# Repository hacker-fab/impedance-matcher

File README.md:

# Automated Impedance Matcher

Teensy 4.1 control loop firmware, custom PCB/CAD hardware, and Python telemetry logging/plotting tools.

## Layout

```
├── firmware/
│   ├── impedance_matcher/                 # Tuning loop, local UI, & motor controls
│   ├── headless_matcher/                  # Serial-only sketch
│   ├── live.py                            # Serial reader, live plots, CSV logger
│   └── plot.py                            # Offline plots & Mermaid export
└── hardware/
    ├── CAD/                               # Mechanical design & enclosure models
    └── PCB/                               # KiCad project & manufacturing files
        ├── impedance_matcher.kicad_pro    # KiCad project main file
        ├── spice/                         # SPICE verification of analog support circuits
        └── production/                    # JLCPCB manufacturing & assembly
            ├── imp_match.zip              # Gerbers
            ├── imp_match_bom.csv          # Assembly BOM
            └── imp_match_positions.csv    # Component placement
```

**Arduino libraries:** Adafruit SSD1306, Adafruit GFX, and TMCStepper (GUI build); TMCStepper only for headless.

## Firmware

- **GUI:** Gradient-style matching toward lower VSWR; loop runs matching, encoder poll, then OLED refresh.
- **Headless:** Same matching; control via serial (`stream on`, `help`, etc.).

Serial is **500000** baud unless you change it in code and in `live.py`.

## Live telemetry

- Default CSV path is `data/csv/latest.csv`.
- Enable **`VSWR_CSV`** lines from the device: **USB log** in settings, or `stream on` in headless.

```bash
# From repo root; adjust --port to your Teensy
python firmware/live.py --port /dev/cu.usbmodemXXXX --window-seconds 20
```

## Offline plots

- Loads the 8-column telemetry CSV, drops bad/outlier rows, then plots VSWR, motors, and match state.
- **Matplotlib** is the default windowed plot.
- **Plotly:** `--interactive` (browser) or `--html`.
- **Mermaid:** `--mermaid` writes `data/mermaid/<csv_stem>_{vswr,motor1,motor2,match}.mmd`.
```bash
python firmware/plot.py path/to/run.csv
python firmware/plot.py path/to/run.csv --minutes --sample-interval 0.25
python firmware/plot.py path/to/run.csv --interactive
python firmware/plot.py path/to/run.csv --html
python firmware/plot.py path/to/run.csv --mermaid
```

## Telemetry CSV format

Written by `live.py` (and compatible with `plot.py`):

`host_time_s,device_millis,vswr,forward_v,reverse_v,motor1_pos_rad,motor2_pos_rad,at_match`

## Hardware notes

The analog support circuits have limited DC SPICE benches and worst-case
calculations; see `hardware/PCB/spice/` for their assumptions and limits.

`MATCHING_USE_DRIVER_UART` defaults to `0` in
`firmware/impedance_matcher/include/config.h` for standalone STEP/DIR. Set it to
`1` to enable TMC2209 UART. To return to standalone, reflash with `0` and fully
power-cycle both drivers (VM and VIO); a Teensy-only reset does not clear their
registers.

Before using external 5 V and USB together, isolate the Teensy's VIN–VUSB link
following [PJRC's power instructions](https://www.pjrc.com/store/teensy41.html).

## Authors

- Miguel Salvacion
- William Gao

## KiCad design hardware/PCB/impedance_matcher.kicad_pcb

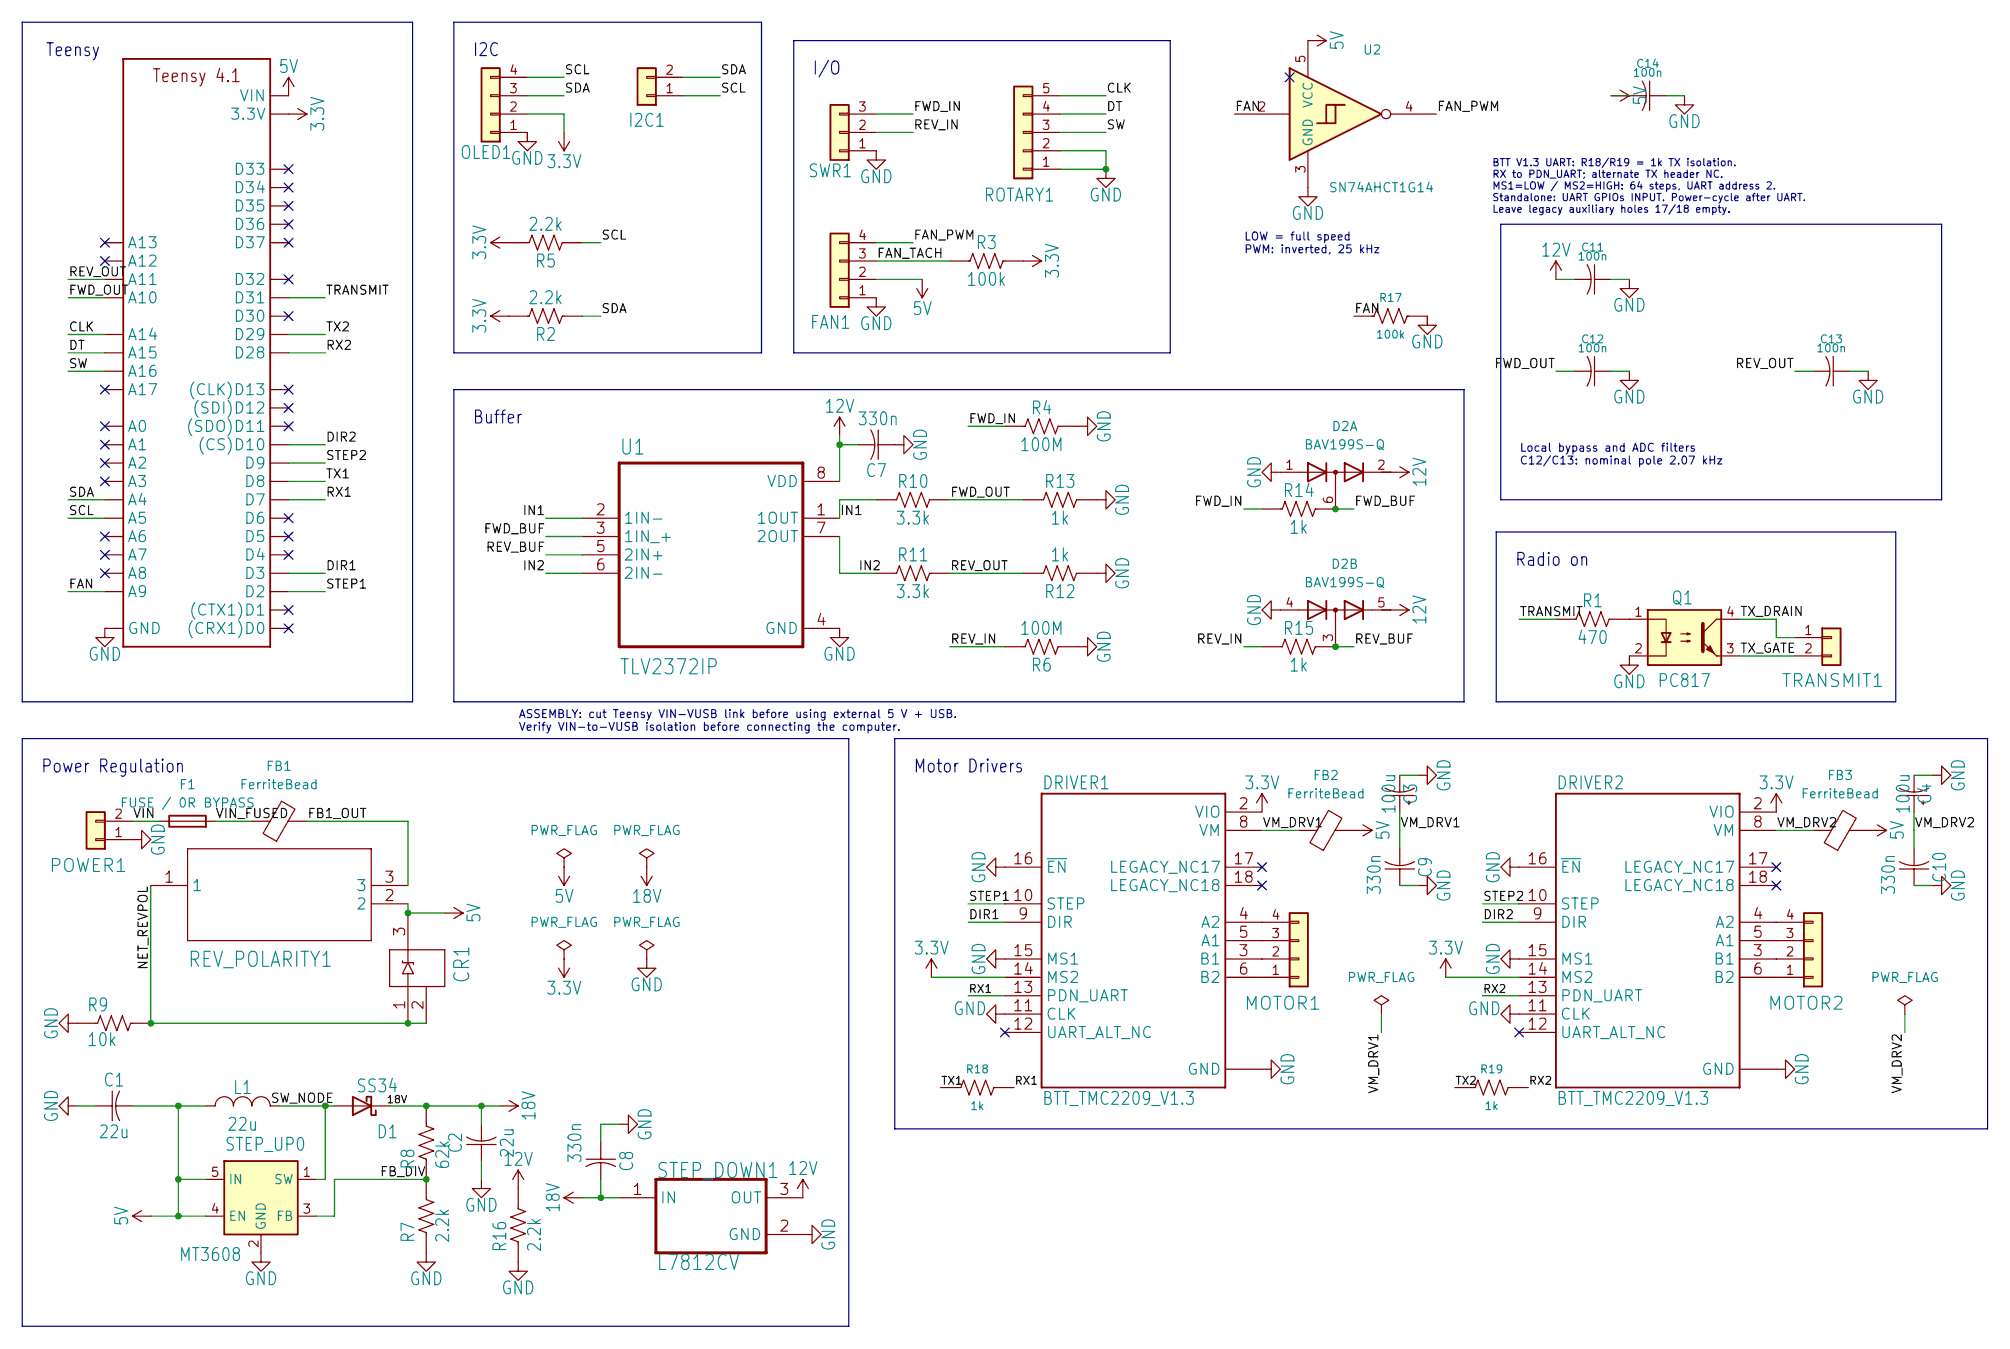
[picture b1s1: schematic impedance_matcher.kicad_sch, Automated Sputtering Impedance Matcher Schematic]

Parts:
A1: TEENSY_4.1; TEENSY_LONG_EXT; MPN TEENSY41
C1, C2: 22u; CAPC2012X110; MPN CL21A226MAQNNNE; LCSC Part C45783
C3, C4: 100u; CP_Radial_D5.0mm_P5.08mm_Formed; MPN EEU-FR1C101B
C7, C8, C9, C10: 330n; CAPC2012X110; MPN 0805B334K500NT; LCSC Part C1740
C11, C12, C13, C14: 100n; CAPC2012X110; MPN CC0805KRX7R9BB104; LCSC Part C49678
CR1: BZX84C5V6; SOT95P240X110-3N; MPN BZX84C5V6; LCSC Part C148101
D1: SS34; SMB_ONS; MPN SS34; LCSC Part C8678
D2: BAV199S-Q; SOT-363_SC-70-6; MPN BAV199S-QZ; LCSC Part C7507590
DRIVER1, DRIVER2: BTT_TMC2209_V1.3; MODULE_TMC2209_SILENTSTEPSTICK; MPN TMC2209 V1.3
F1: FUSE / 0R BYPASS; Fuse_1206_3216Metric
FAN1: Conn_01x04; JST_PH_B4B-PH-K_1x04_P2.00mm_Vertical; MPN B4B-PH-K-S
FB1, FB2, FB3: FerriteBead; L_0805_2012Metric; MPN MPZ2012S101AT000; LCSC Part C15957
I2C1: Conn_01x02; JST_PH_B2B-PH-K_1x02_P2.00mm_Vertical; MPN B2B-PH-K-S
L1: 22u; INDM5450X580; MPN SMNR5040-220MT; LCSC Part C9391
MOTOR1, MOTOR2: Conn_01x04; JST-4-PTH-VERT; MPN B4B-PH-K-S
OLED1: Conn_01x04; JST_PH_B4B-PH-K_1x04_P2.00mm_Vertical; MPN B4B-PH-K-S
POWER1: Conn_01x02; 1X02_2.54_SCREWTERM; MPN PRT-10571
Q1: PC817; DIP762W50P254L650H455Q4B; MPN PC817B; LCSC Part C20612593
R1: 470; RESC2012X65; MPN 0805W8F4700T5E; LCSC Part C17710
R2, R5, R7: 2.2k; RESC2012X65; MPN 0805W8F2201T5E; LCSC Part C17520
R3, R17: 100k; RESC2012X65; MPN 0805W8F1003T5E; LCSC Part C149504
R4, R6: 100M; RESC2012X65; MPN RC0805JR-07100ML; LCSC Part C137480
R8: 62k; RESC2012X65; MPN 0805W8F6202T5E; LCSC Part C17783
R9: 10k; RESC2012X65; MPN 0805W8F1002T5E; LCSC Part C17414
R10, R11: 3.3k; RESC2012X65; MPN 0805W8F3301T5E; LCSC Part C26010
R12, R13, R14, R15, R18, R19: 1k; RESC2012X65; MPN 0805W8F1001T5E; LCSC Part C17513
R16: 2.2k; R_0805_2012Metric; MPN 0805W8F2201T5E; LCSC Part C17520
REV_POLARITY1: DMP6180SK3-13TO252_DMP6180SK3_DIO; TO252_DMP6180SK3_DIO; MPN DMP6180SK3-13; LCSC Part C93034
ROTARY1: Conn_01x05; JST_PH_B5B-PH-K_1x05_P2.00mm_Vertical; MPN B5B-PH-K-S
STEP_DOWN1: L7812CV; TO-220-3; MPN L7812CV; LCSC Part C105651
STEP_UP0: MT3608; SOT95P280X145-6N; MPN MT3608; LCSC Part C84817
SWR1: JST_03; JST_PH_B3B-PH-K_1x03_P2.00mm_Vertical; MPN B3B-PH-K-S
TRANSMIT1: Conn_01x02; 1X02_2.54_SCREWTERM; MPN PRT-10571
U1: TLV2372IP; DIP794W45P254L959H508Q8; MPN TLV2372IP; LCSC Part C2878991
U2: SN74AHCT1G14; SOT-23-5; MPN SN74AHCT1G14DBVR; LCSC Part C55250

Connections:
3.3V: A1.3V3 (3.3V), A1.3V3@2 (3.3V), DRIVER1.2 (VIO_2), DRIVER1.14 (MS2_14), DRIVER2.2 (VIO_2), DRIVER2.14 (MS2_14), OLED1.2, R2.2, R3.2, R5.2
5V: A1.VIN, C1.2, C14.2, CR1.3, FAN1.2, FB2.2, FB3.2, L1.1, REV_POLARITY1.2, STEP_UP0.4 (EN), STEP_UP0.5 (IN), U2.5 (VCC)
12V: C7.2, C11.2, D2.2 (K2), D2.5 (K4), R16.2, STEP_DOWN1.3 (OUT), U1.8 (VDD)
18V: C2.2, C8.2, D1.1 (K), R8.2, STEP_DOWN1.1 (IN)
/CLK: A1.D38 (A14), ROTARY1.5
/DIR1: A1.D3, DRIVER1.9 (DIR_9)
/DIR2: A1.D10 ((CS)D10), DRIVER2.9 (DIR_9)
/DT: A1.D39 (A15), ROTARY1.4
/FAN: A1.D23 (A9), R17.1, U2.2
/FAN_PWM: FAN1.4, U2.4
/FAN_TACH: FAN1.3, R3.1
/FB1_OUT: FB1.2, REV_POLARITY1.3
/FB_DIV: R7.2, R8.1, STEP_UP0.3 (FB)
/FWD_BUF: D2.6 (K3A4), R14.2, U1.3 (1IN_+)
/FWD_IN: R4.1, R14.1, SWR1.3
/FWD_OUT: A1.D24 (A10), C12.2, R10.2, R13.1
/IN1: R10.1, U1.1 (1OUT), U1.2 (1IN-)
/IN2: R11.1, U1.6 (2IN-), U1.7 (2OUT)
/NET_REVPOL: CR1.1, CR1.2, R9.2, REV_POLARITY1.1
/REV_BUF: D2.3 (K1A2), R15.2, U1.5 (2IN+)
/REV_IN: R6.2, R15.1, SWR1.2
/REV_OUT: A1.D25 (A11), C13.2, R11.2, R12.2
/RX1: A1.D7, DRIVER1.13 (PDN_UART), R18.2
/RX2: A1.D28, DRIVER2.13 (PDN_UART), R19.2
/SCL: A1.D19 (A5), I2C1.1, OLED1.4, R5.1
/SDA: A1.D18 (A4), I2C1.2, OLED1.3, R2.1
/STEP1: A1.D2, DRIVER1.10 (STEP_10)
/STEP2: A1.D9, DRIVER2.10 (STEP_10)
/SW: A1.D40 (A16), ROTARY1.3
/SW_NODE: D1.2 (A), L1.2, STEP_UP0.1 (SW)
/TRANSMIT: A1.D31, R1.1
/TX1: A1.D8, R18.1
/TX2: A1.D29, R19.1
/TX_DRAIN: Q1.4, TRANSMIT1.1
/TX_GATE: Q1.3, TRANSMIT1.2
/VIN: F1.1, POWER1.2
/VIN_FUSED: F1.2, FB1.1
/VM_DRV1: C3.1 (+), C9.2, DRIVER1.8 (VM_8), FB2.1
/VM_DRV2: C4.1 (+), C10.2, DRIVER2.8 (VM_8), FB3.1
GND: A1.AGND/GND (GND), A1.GND, A1.GND@2 (GND), C1.1, C2.1, C3.2 (-), C4.2 (-), C7.1, C8.1, C9.1, C10.1, C11.1, C12.1, C13.1, C14.1, D2.1 (A1), D2.4 (A3), DRIVER1.1 (GND_1), DRIVER1.7 (GND_7), DRIVER1.11 (CLK), DRIVER1.15 (MS1_15), DRIVER1.16 (~EN_16), DRIVER2.1 (GND_1), DRIVER2.7 (GND_7), DRIVER2.11 (CLK), DRIVER2.15 (MS1_15), DRIVER2.16 (~EN_16), FAN1.1, OLED1.1, POWER1.1, Q1.2, R4.2, R6.1, R7.1, R9.1, R12.1, R13.2, R16.1, R17.2, ROTARY1.1, ROTARY1.2, STEP_DOWN1.2 (GND), STEP_UP0.2 (GND), SWR1.1, U1.4 (GND), U2.3 (GND)
unnamed: DRIVER1.5 (A1), MOTOR1.3
unnamed: DRIVER1.4 (B1), MOTOR1.4
unnamed: DRIVER1.3 (B2), MOTOR1.2
unnamed: DRIVER1.6 (A2), MOTOR1.1
unnamed: DRIVER2.5 (A1), MOTOR2.3
unnamed: DRIVER2.4 (B1), MOTOR2.4
unnamed: DRIVER2.3 (B2), MOTOR2.2
unnamed: DRIVER2.6 (A2), MOTOR2.1
unnamed: Q1.1, R1.2

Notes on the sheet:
LOW = full speed PWM: inverted, 25 kHz
I2C
Motor Drivers
Power Regulation
Radio on
I/O
Local bypass and ADC filters C12/C13: nominal pole 2.07 kHz
Teensy
ASSEMBLY: cut Teensy VIN-VUSB link before using external 5 V + USB. Verify VIN-to-VUSB isolation before connecting the computer.
Buffer
BTT V1.3 UART: R18/R19 = 1k TX isolation. RX to PDN_UART; alternate TX header NC. MS1=LOW / MS2=HIGH: 64 steps, UART address 2. Standalone: UART GPIOs INPUT. Power-cycle after UART. Leave legacy auxiliary holes 17/18 empty.

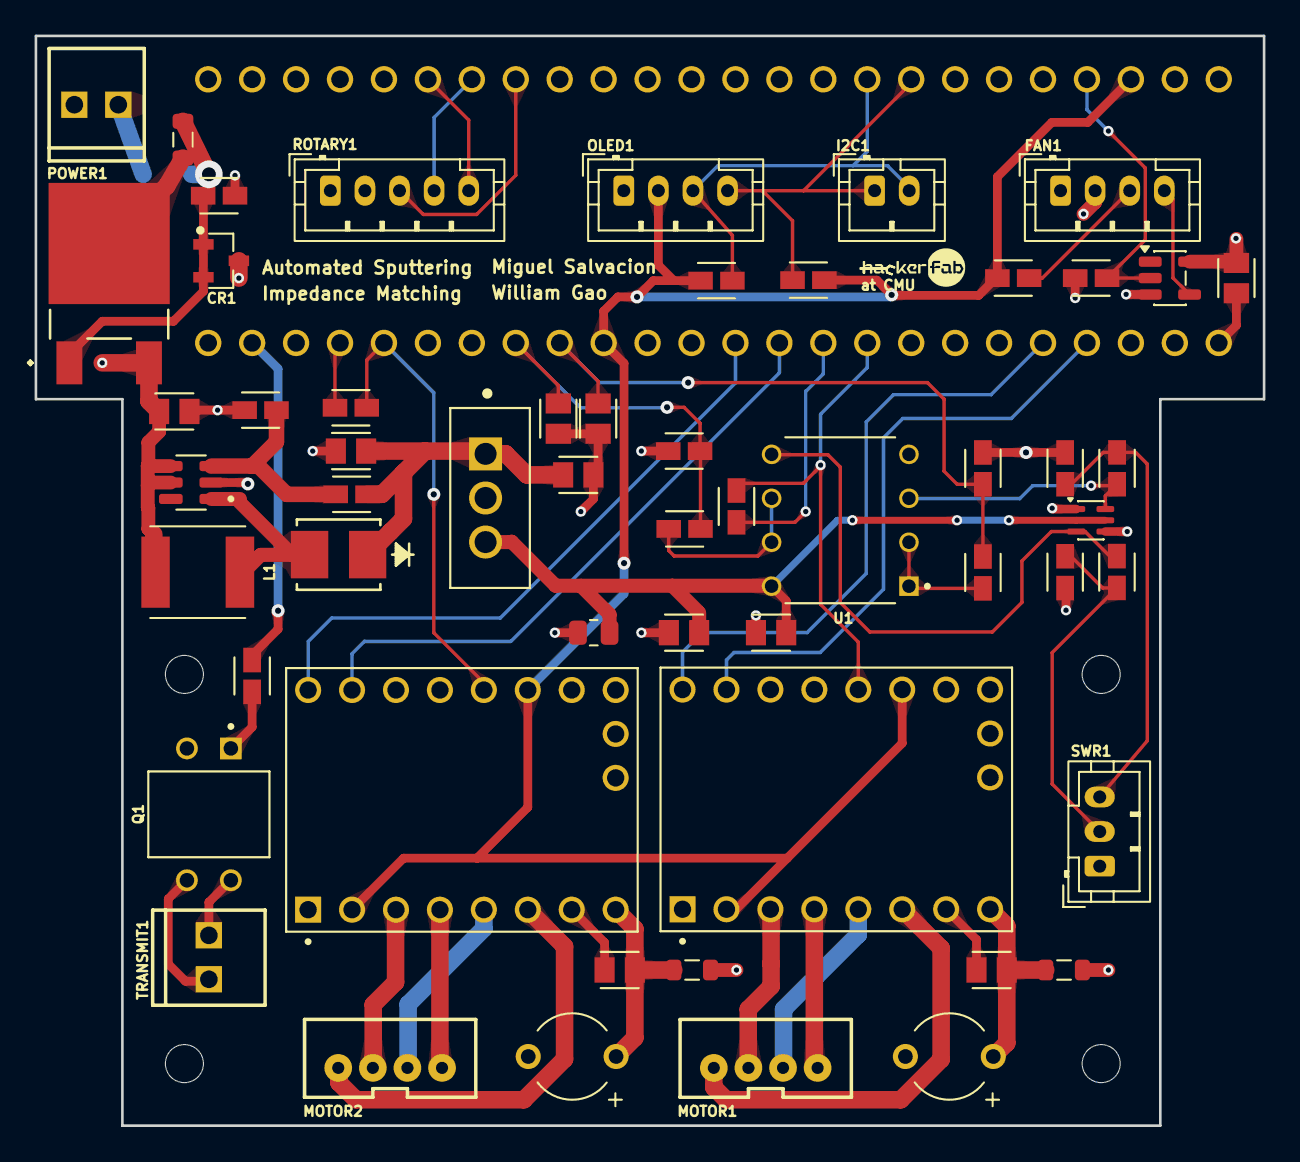
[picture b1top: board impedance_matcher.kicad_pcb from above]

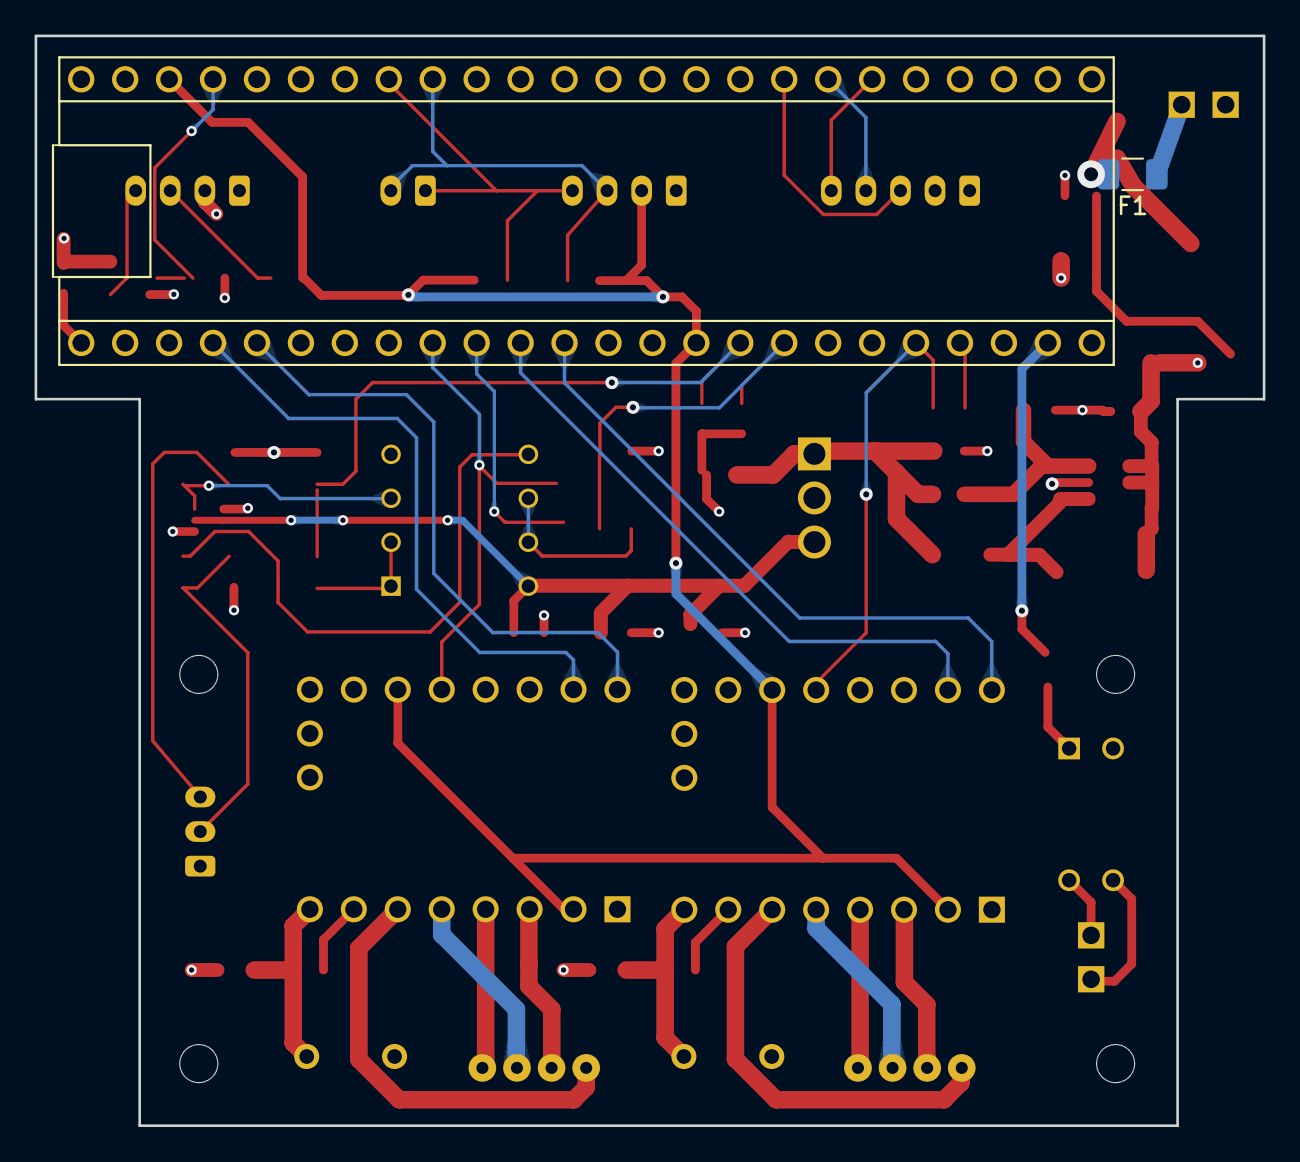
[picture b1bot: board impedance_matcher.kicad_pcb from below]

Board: 4 copper layers, 71.0 x 63.0 mm, 57 parts (2 on the bottom side), 49 nets.

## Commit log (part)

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2026-04-30 Visualize csv data
2026-04-30 Combined screen code with matching code
2026-05-01 Removed .DS_Store metedata
2026-05-01 Reogranize repo and add PCB files
2026-05-01 Licensing
2026-05-02 Refined headless mode
2026-06-09 KiCad files
2026-06-09 Small PCB fixes
2026-06-09 Add some 3D models
2026-06-09 More PCB fixes
2026-06-09 All 3D models
2026-06-09 New gerbers
2026-06-09 Update README again
2026-06-11 Move capacitor closer to op-amp VDD
2026-06-11 Switch to 4 layer PCB and add ferrite beads
2026-06-15 Switch all resistors to 0805
2026-06-15 Small fixes
